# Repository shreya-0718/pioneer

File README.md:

# Pioneer 🪐

a PCB fidget toy!

First of all, thank you Meghana for the awesome YSWS https://pathfinder.hackclub.com/! We stan Meghana <3

This is a board I made for the Pathfinder YSWS by Hack Club. And now for a mini yap session
about the name and why I chose it:

## Inspiration ✨
The word Pathfinder inspired the word Pioneer, and since I knew I wanted four buttons (and of course four LEDs), I used each of the buttons to represent the different "eras" of exploration. Here were the four symbols I came up with (which I will paint on the four buttons): a foot 👣 (whenever I say foot y'all I mean the footprint, not an actual foot 😭 I realized that a little late so I added emojis in here for visualization), a compass 🧭, a train 🚂, and a rocket 🚀. Each era, when activated, makes the LEDs do something new depending on what script you are in.

And then of course the empty space was kind of sad, so I thought, why not add stars and planets? The final design has three LEDs as planets, one as the sun (so 4 LEDs total), a couple constellations silkscreened onto it, and a LOT of stars. Plus, of course, the four buttons. The rocket one couldn't fit in a neat little row with the other three, so it's hovering above the XIAO microcontroller. Which I convinced myself was fitting because it looks like it's launching into space. 

My final goal for making this project was to learn get more experience with PCBs on Kicad and microcontrollers (especially before I dived into HackPad and potentially more complicated hardware projects in the future)! And there are multiple scripts you can run on this board, which I will explain below.

So, as it turns out... this board doesn't just have one script you can run on it. Or two, or three. It has four! Here are the four scripts you can run, and what the four buttons do in each of them:

### Awaken 🌞
This is the first script I wrote for this board. It's a nice little animation script, where the LEDs seem to dance. Since it was the first script, it was like the "awakening" of the board, hence the name (the other name idea I had was "Bling" since it makes the LEDs go blingy blingy and look pretty). Here are what each of the buttons do in this script:

| Button     | Description |
|----------|-------------|
| 👣 Foot   | Turns on the sun (LED4) with a soft pulse. Press again to turn it off. |
| 🧭 Compass | Starts a slow orbit animation of the three planet LEDs around the sun. Press again to reverse direction |
| 🚂 Train  | LEDs blink in rhythm to a steady beat |
| 🚀 Rocket | Like a little launch sequence: the four LEDs light up in order, then all flash flash and stay on. |

### Signal 📡
This script is all about Morse code! Here’s how it works:
| Button     | Description |
|----------|-------------|
| 👣 Foot   | adds a dot to the message (short blink)|
| 🧭 Compass | adds a dash to the message (long blink) |
| 🚂 Train  | pressed once, adds an inter-letter space (gap). pressed twice in a row adds an inter-word space (longer gap) |
| 🚀 Rocket | sends the Morse code message, the LEDs start flashing |

### Orbit 🌌
This script is a timer that can be used to count down from any number of minutes, in intervals of 5, from 5 to 60 minutes. Here is what the buttons do:
| Button     | Description |
|----------|-------------|
| 👣 Foot   | adds 5 minutes per press. wraps at 60 mins. The LEDs light up in intervals to kind of show how much time has been added|
| 🧭 Compass | pauses or unpauses the timer. when paused, all the LEDs flash slowly. |
| 🚂 Train  | flashes all LEDs 3 times, then resets everything. time = 0, LEDs off|
| 🚀 Rocket | starts the timer! before starting, all currently lit LEDs flash twice. then they stay on, and countdown starts|

What are the time intervals? Here’s how the LEDs light up:
- 5 to 19 min -> LED1
- 20 to 34 min -> LED1 + LED2
- 35 to 49 min -> LED1 + LED2 + LED3
- 50 to 60 min -> all 4 LEDs

### Moonlight 🌚
This script creates a calming moonlight effect that can be used for meditation or as a nightlight! 
There are four modes:
- 🌫️ Mist — unified breathing; the LEDs pulse
- 🌊 Tide — all the LEDs turn on, then all go off, one by one
- ✨ Firefly — independent LED rhythms
- 🌙 Moonlit — triggered by the Train button. one LED pulses softly and shifts on press

Here's what each of the buttons do:

| Button     | Description |
|----------|-------------|
| 👣 Foot   | cycles the brightness between off -> low -> medium -> high  |
| 🧭 Compass | pauses or unpauses the animation of the lights (whereever they are in the cycle)|
| 🚂 Train  | starts/controls Moonlit mode |
| 🚀 Rocket | cycles modes between Mist, Tide, and Firefly |

## Built With 🛠️

- XIAO RP2040 Microcontroller
- 4 Cherry MX Buttons + Switches
- 4 LEDs (random colors)

I used KiCad for the PCB, and VSCode with Arduino for the firmware part of it.

## Learning 🌱
This wasn't my first time using KiCad, but it was my first time using the XIAO microcontroller. I also learned how to write firmware for it using Arduino. The hardest part was figuring out the logic for the scripts, considering I had so many moving parts and buttons to handle, and to make sure that clicking two buttons at the same time didn't make the LEDs go wild. Overall, I learned how to use the XIAO RP2040, and will use this knowledge to make the HackPad, and how to write firmware (although as I understand, HackPad code uses either kmk or qmk).

## Images! 📸
Here is my schematic: 

And here's my PCB editor:

And here is the final look!:

I'll add more pictures once I get the board + keys and put this thing together!

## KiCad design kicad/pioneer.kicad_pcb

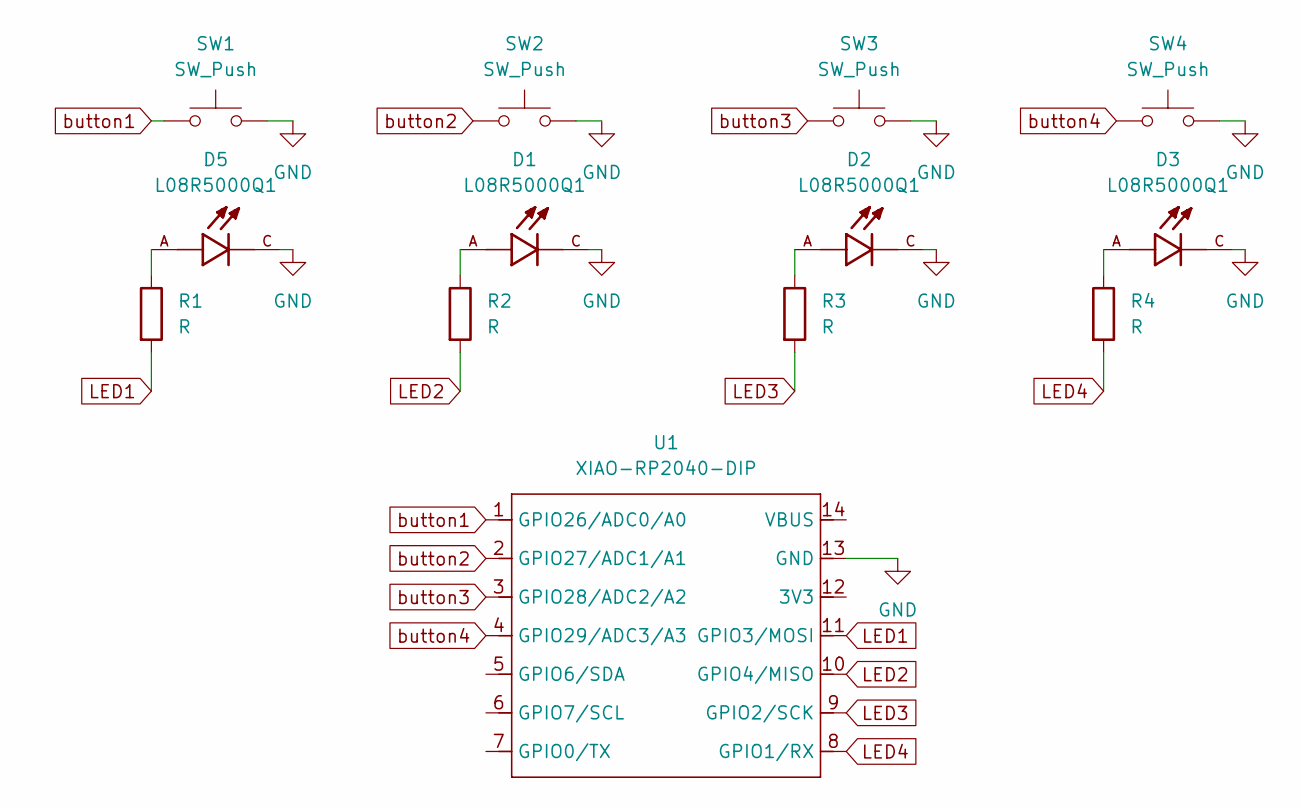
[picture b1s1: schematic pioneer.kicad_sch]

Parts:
D1, D2, D3, D5: L08R5000Q1; LEDRD254W57D500H1070; PARTREV NA
R1, R2, R3, R4: R; R_Axial_DIN0204_L3.6mm_D1.6mm_P5.08mm_Horizontal
SW1, SW2, SW3, SW4: SW_Push; SW_Cherry_MX_1.00u_PCB
U1: XIAO-RP2040-DIP

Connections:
GND: D1.C, D2.C, D3.C, D5.C, SW1.2, SW2.2, SW3.2, SW4.2, U1.13 (GND)
LED1: R1.2, U1.11 (GPIO3/MOSI)
LED2: R2.2, U1.10 (GPIO4/MISO)
LED3: R3.2, U1.9 (GPIO2/SCK)
LED4: R4.2, U1.8 (GPIO1/RX)
unnamed: D1.A, R2.1
unnamed: D2.A, R3.1
unnamed: D3.A, R4.1
unnamed: D5.A, R1.1
button1: SW1.1, U1.1 (GPIO26/ADC0/A0)
button2: SW2.1, U1.2 (GPIO27/ADC1/A1)
button3: SW3.1, U1.3 (GPIO28/ADC2/A2)
button4: SW4.1, U1.4 (GPIO29/ADC3/A3)

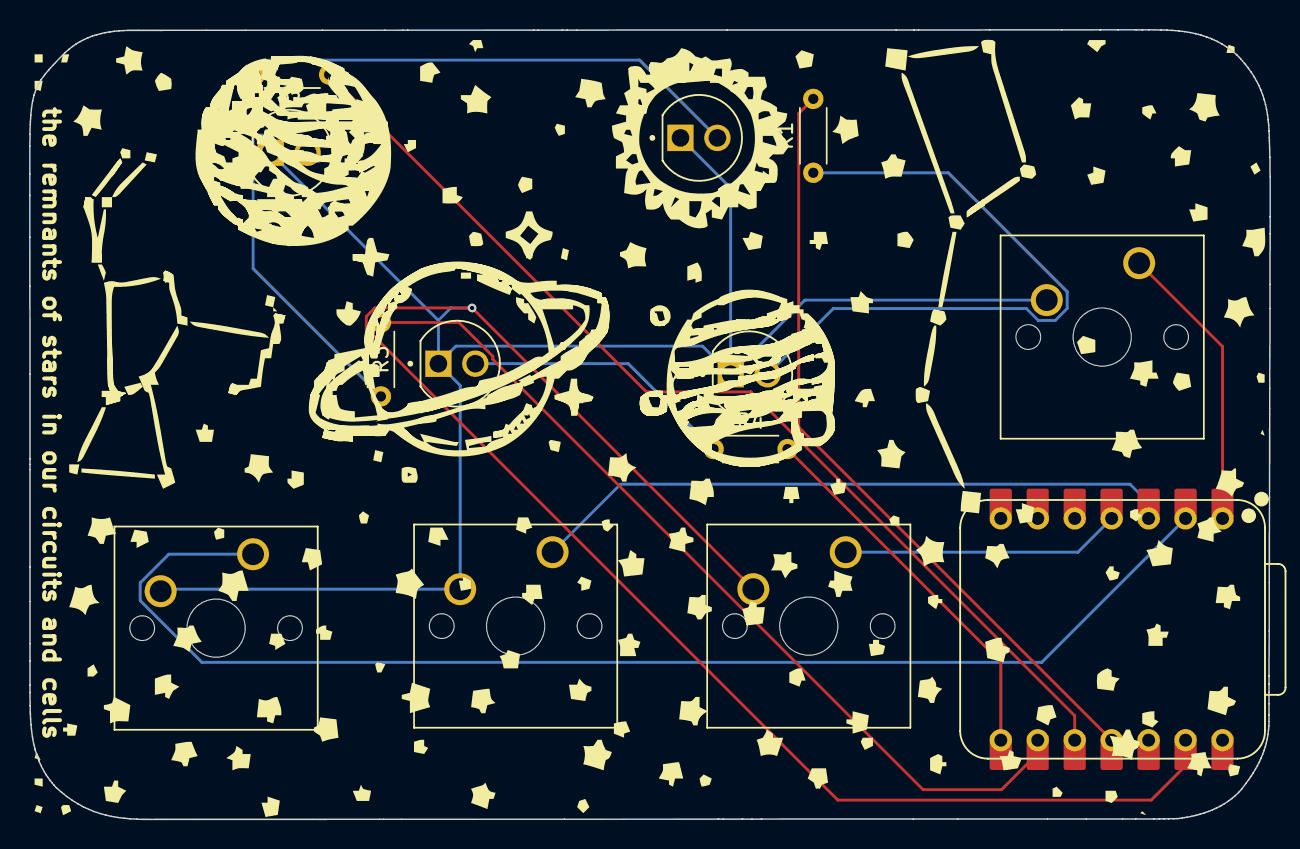
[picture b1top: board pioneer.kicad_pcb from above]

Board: 2 copper layers, 85.3 x 54.3 mm, 13 parts (0 on the bottom side), 13 nets.

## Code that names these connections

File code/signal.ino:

// #include <Arduino.h>

// Signal - a morse code flasher :)

// Temporary defining pin numbers:
#define D0 0
#define D1 1
#define D2 2
#define D3 3
#define D7 7
#define D8 8
#define D9 9
#define D10 10

// Define button pins
int SEND = D0;
int DOT = D1;
int DASH = D2;
int SPACE = D3;

// Define LED pins
int LED1 = D10; // sun
int LED2 = D9;
int LED3 = D8;
int LED4 = D7;

String morse = "";
bool trainSpace = false; 
// to check if the last button pressed was trainSpace or not

void setup() { 
    pinMode(SEND, INPUT);
    pinMode(DOT, INPUT);
    pinMode(DASH, INPUT);
    pinMode(SPACE, INPUT);

    pinMode(LED1, OUTPUT);
    pinMode(LED2, OUTPUT);
    pinMode(LED3, OUTPUT);
    pinMode(LED4, OUTPUT);

    long startTime = millis();

    digitalWrite(LED1, LOW);
    digitalWrite(LED2, LOW);
    digitalWrite(LED3, LOW);
    digitalWrite(LED4, LOW);
}

void loop() {
    if (digitalRead(DOT) == HIGH) {
        morse += ".";
        trainSpace = false;
        delay(300);
    }

    if (digitalRead(DASH) == HIGH) {
        morse += "_";
        trainSpace = false;
        delay(300);
    }
    if (digitalRead(SPACE) == HIGH) {
        if (trainSpace) {
            morse += "  "; // word space
            trainSpace = false;
        } else {
            morse += " "; // letter space
            trainSpace = true;
        }

        delay(300);
    }

    if (digitalRead(SEND) == HIGH) {
        flashAll(2); // flashes ALL LEDs
        sendMorse(morse);
        flashAll(2);

        trainSpace = false;

        delay(1000);
    }
}

void sendMorse(String code) {
    for (int i = 0; i < code.length(); i++) {
        char c = code[i];

        // word space: three consecutive spaces
        if (c == ' ' && i + 1 < code.length() && code[i + 1] == ' ') {
            delay(1400);
            i++;
            continue;
        }

        if (c == '.') blinkDot();
        else if (c == '_') blinkDash();
        else if (c == ' ') delay(600); // letter space

        // space between symbols unless the next character is a space
        if (i < code.length() - 1 && code[i + 1] != ' ') delay(200);
    }
}

void blinkDot() {

}

void blinkDash() {

}

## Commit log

2025-06-29 added all KiCad files!
2025-06-29 added Arduino code
2025-06-29 Update README.md with project details, inspiration, functions, and learning experiences
2025-06-29 added images to README
2025-06-29 changed pioneer.ino to awaken.ino to allow for more scripts
2025-06-29 Updating awaken.ino and adding to planning.txt
2025-06-30 Started writing a new script: to make my board able to flash morse code!
2025-06-30 started and working on a timer logic script!
2025-06-30 finished the code for Orbit, the timer script for Pioneer!
2025-07-01 finished the code for the fourth and final script of pioneer... Moonlight!
2025-07-02 Updated README.md with the new scripts and their functions!
2025-07-02 Updated project KiCad files
2025-07-02 Updated pcb_back image and added a picture of the PCB editor in README.md
2025-07-04 Refined README.md
